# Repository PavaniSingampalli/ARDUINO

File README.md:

# ARDUINO
A simple version of ARDUINO is designed using atmega328p microcontroller to implement real time projects.

This repository contains the following:

1.Eagle schematic file

2.Eagle board file

3.Gerbers

4.PDFs of the schematic and the board files

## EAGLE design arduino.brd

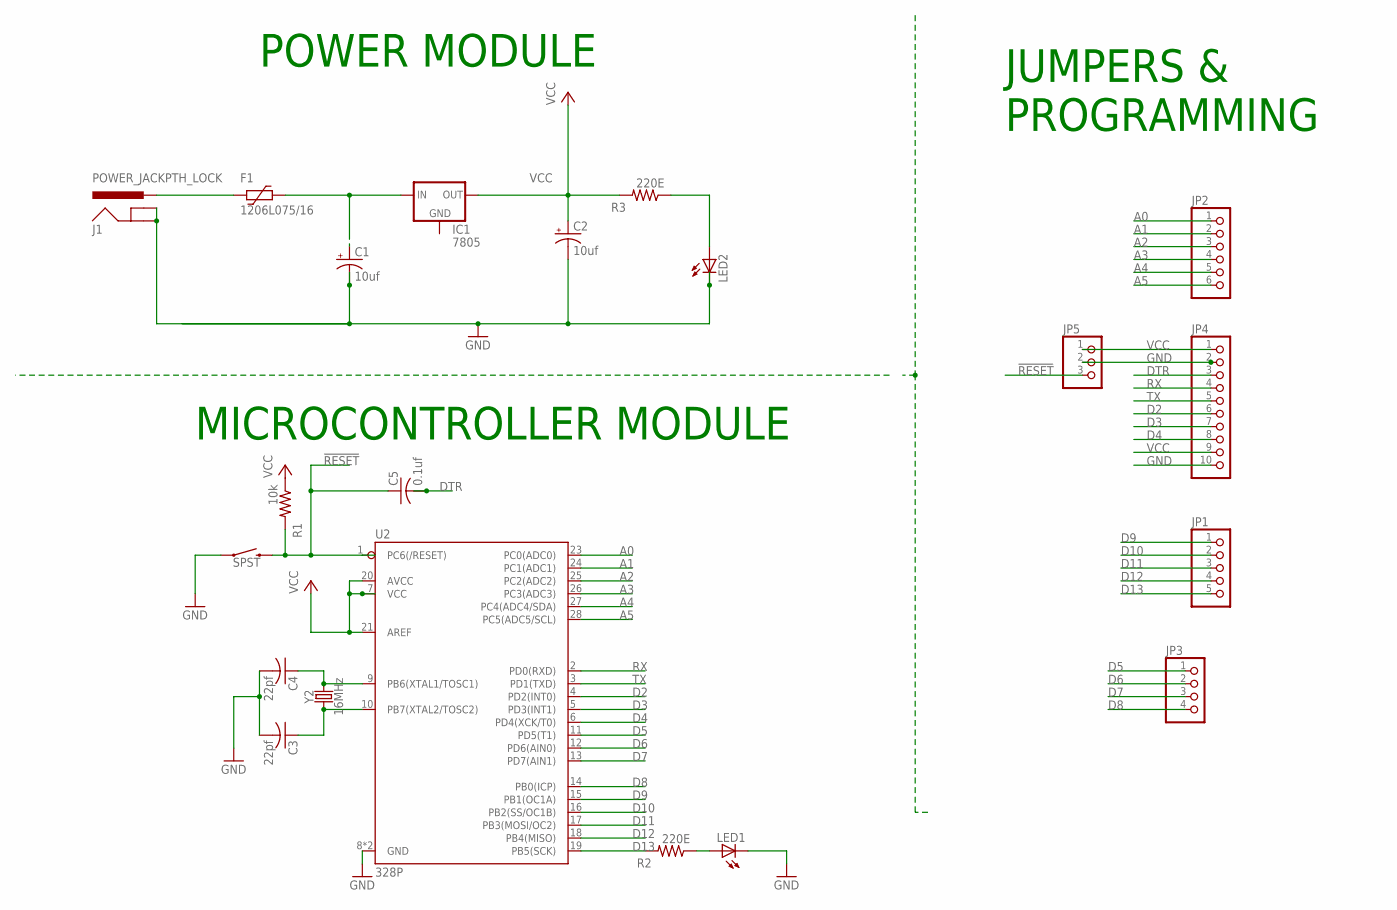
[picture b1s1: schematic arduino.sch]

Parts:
C1, C2: 10uf; E2,5-6E
C3, C4: 22pf; C025-024X044
C5: 0.1uf; C025-024X044
F1: 1206L075/16; 1206L
IC1: 7805; 78XXS
J1: POWER_JACKPTH_LOCK; POWER_JACK_PTH_LOCK
JP1: PINHD-1X5; 1X05
JP2: PINHD-1X6; 1X06
JP3: PINHD-1X4; 1X04
JP4: PINHD-1X10; 1X10
JP5: PINHD-1X3; 1X03
LED1, LED2: LED3MM
R1: 10k; 0204/7
R2, R3: 220E; 0204/7
S2: SPST; TACTILE_SWITCH_PTH_6.0MM
U2: 328P; DIP28
Y2: 16MHz; HC49US

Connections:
!RESET: C5.1, JP5.3, R1.2, S2.3 (2), U2.1 (PC6(/RESET))
A0: JP2.1, U2.23 (PC0(ADC0))
A1: JP2.2, U2.24 (PC1(ADC1))
A2: JP2.3, U2.25 (PC2(ADC2))
A3: JP2.4, U2.26 (PC3(ADC3))
A4: JP2.5, U2.27 (PC4(ADC4/SDA))
A5: JP2.6, U2.28 (PC5(ADC5/SCL))
D2: JP4.6, U2.4 (PD2(INT0))
D3: JP4.7, U2.5 (PD3(INT1))
D4: JP4.8, U2.6 (PD4(XCK/T0))
D5: JP3.1, U2.11 (PD5(T1))
D6: JP3.2, U2.12 (PD6(AIN0))
D7: JP3.3, U2.13 (PD7(AIN1))
D8: JP3.4, U2.14 (PB0(ICP))
D9: JP1.1, U2.15 (PB1(OC1A))
D10: JP1.2, U2.16 (PB2(SS/OC1B))
D11: JP1.3, U2.17 (PB3(MOSI/OC2))
D12: JP1.4, U2.18 (PB4(MISO))
D13: JP1.5, R2.2, U2.19 (PB5(SCK))
DTR: C5.2, JP4.3
GND: C1.-, C2.-, C3.2, C4.2, J1.GND, J1.GNDBREAK, JP4.2, JP4.10, JP5.2, LED1.K (C), LED2.K (C), S2.1, U2.8 (GND), U2.22 (GND)
unnamed: C4.1, U2.9 (PB6(XTAL1/TOSC1)), Y2.2
unnamed: C3.1, U2.10 (PB7(XTAL2/TOSC2)), Y2.1
unnamed: LED1.A, R2.1
unnamed: C1.+, F1.1, IC1.IN
unnamed: F1.2, J1.PWR
unnamed: LED2.A, R3.1
RX: JP4.4, U2.2 (PD0(RXD))
TX: JP4.5, U2.3 (PD1(TXD))
VCC: C2.+, IC1.OUT, JP4.1, JP4.9, JP5.1, R1.1, R3.2, U2.7 (VCC), U2.20 (AVCC), U2.21 (AREF)

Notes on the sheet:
POWER MODULE
MICROCONTROLLER MODULE
JUMPERS & PROGRAMMING

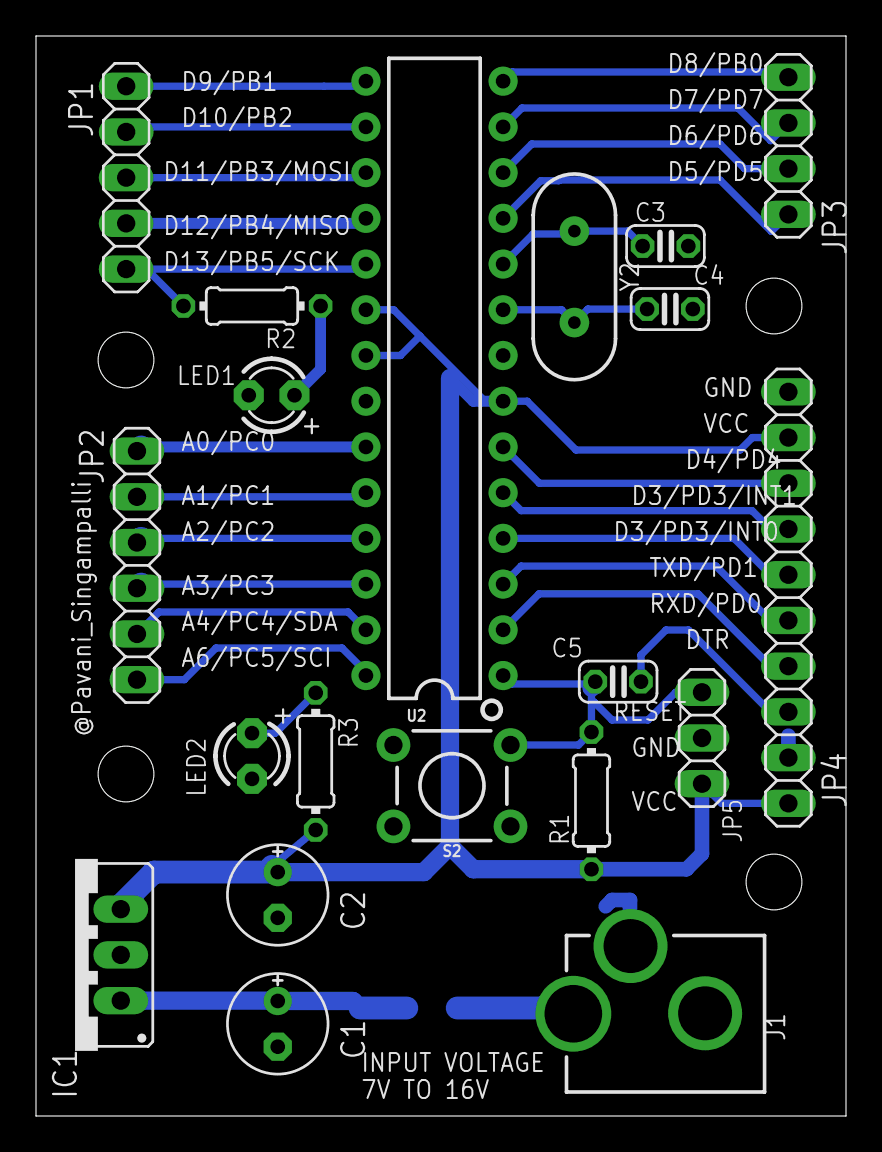
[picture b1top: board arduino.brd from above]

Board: 2 copper layers, 45.0 x 60.0 mm, 21 parts (1 on the bottom side), 30 nets.

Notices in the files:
parts and their libraries:
SparkFun-Connectors: Licensing: Creative Commons ShareAlike 4.0 International - https://creativecommons.org/licenses/by-sa/4.0
